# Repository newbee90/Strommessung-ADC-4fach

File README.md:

# Strommessung-ADC-4fach
nach einem Projekt von Jürgen Stähr, L1,L2,L3 und N auf einem Display
Kontaktlose Strommessung mit ADC für 4 Stromwandler
und Anzeige auf einem 2004 Display

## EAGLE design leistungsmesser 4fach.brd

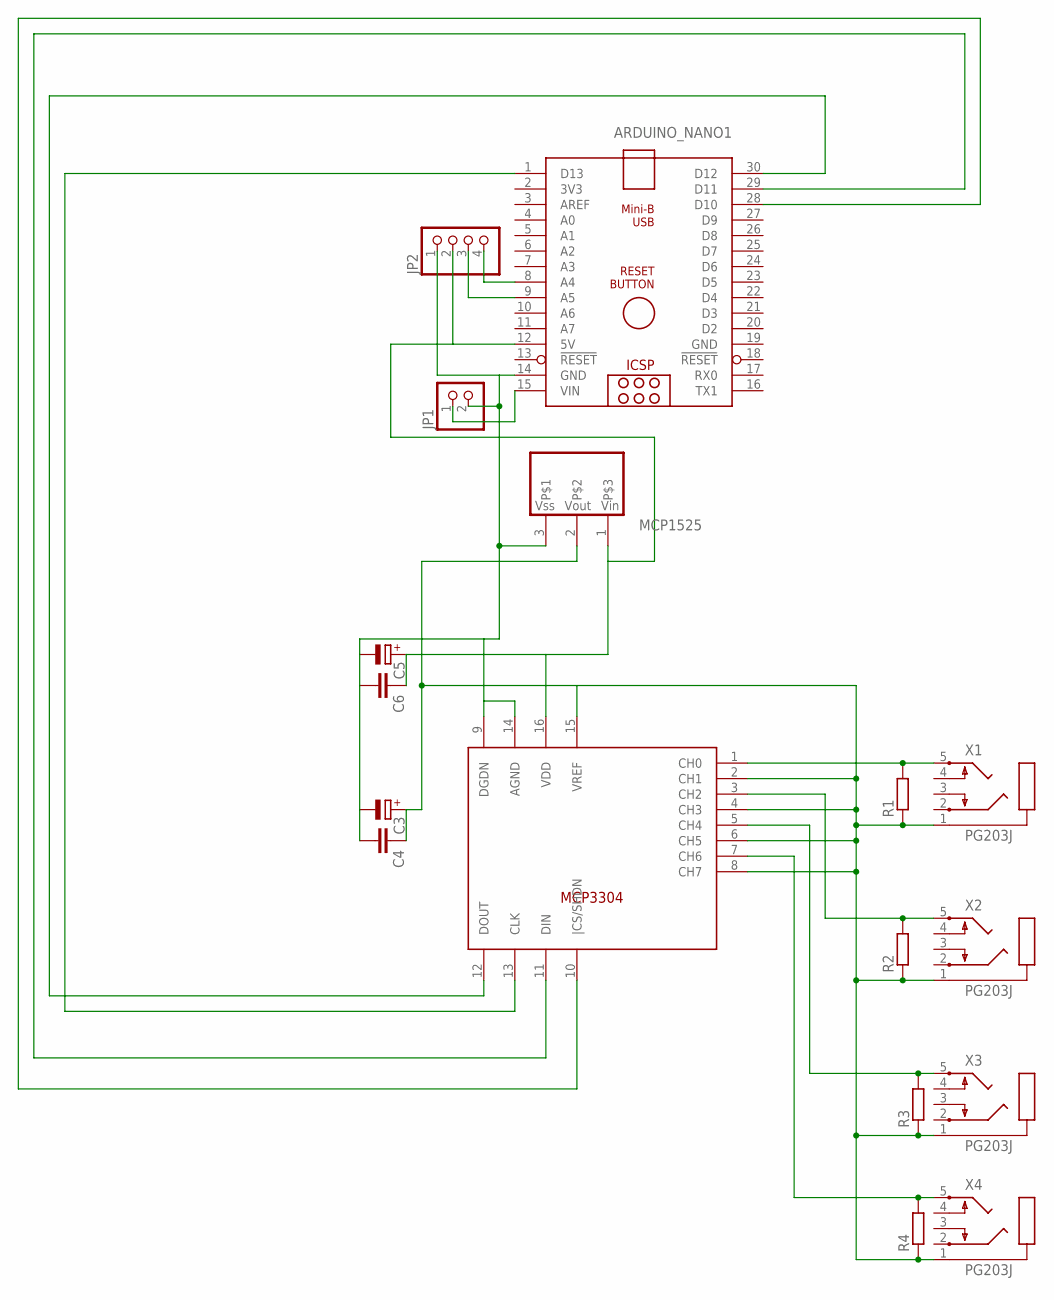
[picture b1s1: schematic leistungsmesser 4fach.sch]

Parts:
ARDUINO_NANO1: ARDUINO_NANO
C3, C5: CPOL-EUE2,5-6E; E2,5-6E
C4, C6: C-EU025-024X044; C025-024X044
IC4: MCP1525; TO92-
JP1: PINHD-1X2; 1X02
JP2: PINHD-1X4; 1X04
R1, R2, R3, R4: R-EU_0309/V; 0309V
U$1: MCP3304; DIP16
X1, X2, X3, X4: PG203J

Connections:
GND: ARDUINO_NANO1.19 (GND)
unnamed: ARDUINO_NANO1.14 (GND), C3.-, C4.2, C5.-, C6.2, IC4.3, JP1.2, JP2.1, U$1.9 (DGDN), U$1.14 (AGND)
unnamed: C3.+, C4.1, IC4.2, R1.1, R2.1, R3.1, R4.1, U$1.2 (CH1), U$1.4 (CH3), U$1.6 (CH5), U$1.8 (CH7), U$1.15 (VREF), X1.1, X2.1, X3.1, X4.1
unnamed: R2.2, U$1.3 (CH2), X2.5
unnamed: ARDUINO_NANO1.30 (D12), U$1.12 (DOUT)
unnamed: ARDUINO_NANO1.15 (VIN), JP1.1
unnamed: ARDUINO_NANO1.28 (D10), U$1.10 (|CS/SHDN)
unnamed: ARDUINO_NANO1.29 (D11), U$1.11 (DIN)
unnamed: ARDUINO_NANO1.1 (D13), U$1.13 (CLK)
unnamed: R3.2, U$1.5 (CH4), X3.5
unnamed: ARDUINO_NANO1.12 (5V), C5.+, C6.1, IC4.1, JP2.2, U$1.16 (VDD)
unnamed: R1.2, U$1.1 (CH0), X1.5
unnamed: R4.2, U$1.7 (CH6), X4.5
unnamed: ARDUINO_NANO1.8 (A4), JP2.4
unnamed: ARDUINO_NANO1.9 (A5), JP2.3

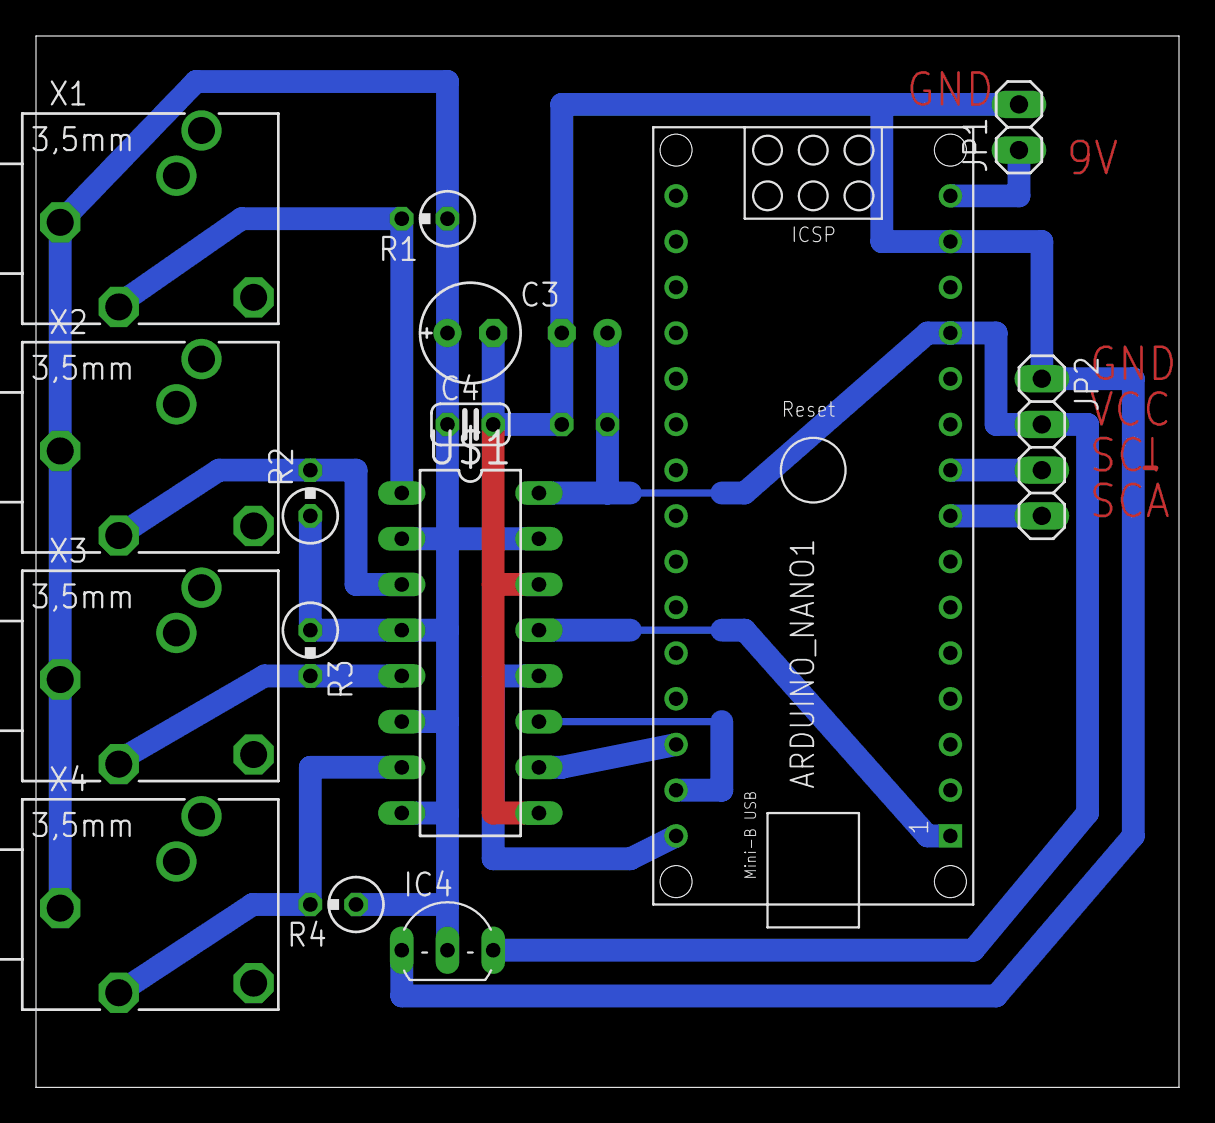
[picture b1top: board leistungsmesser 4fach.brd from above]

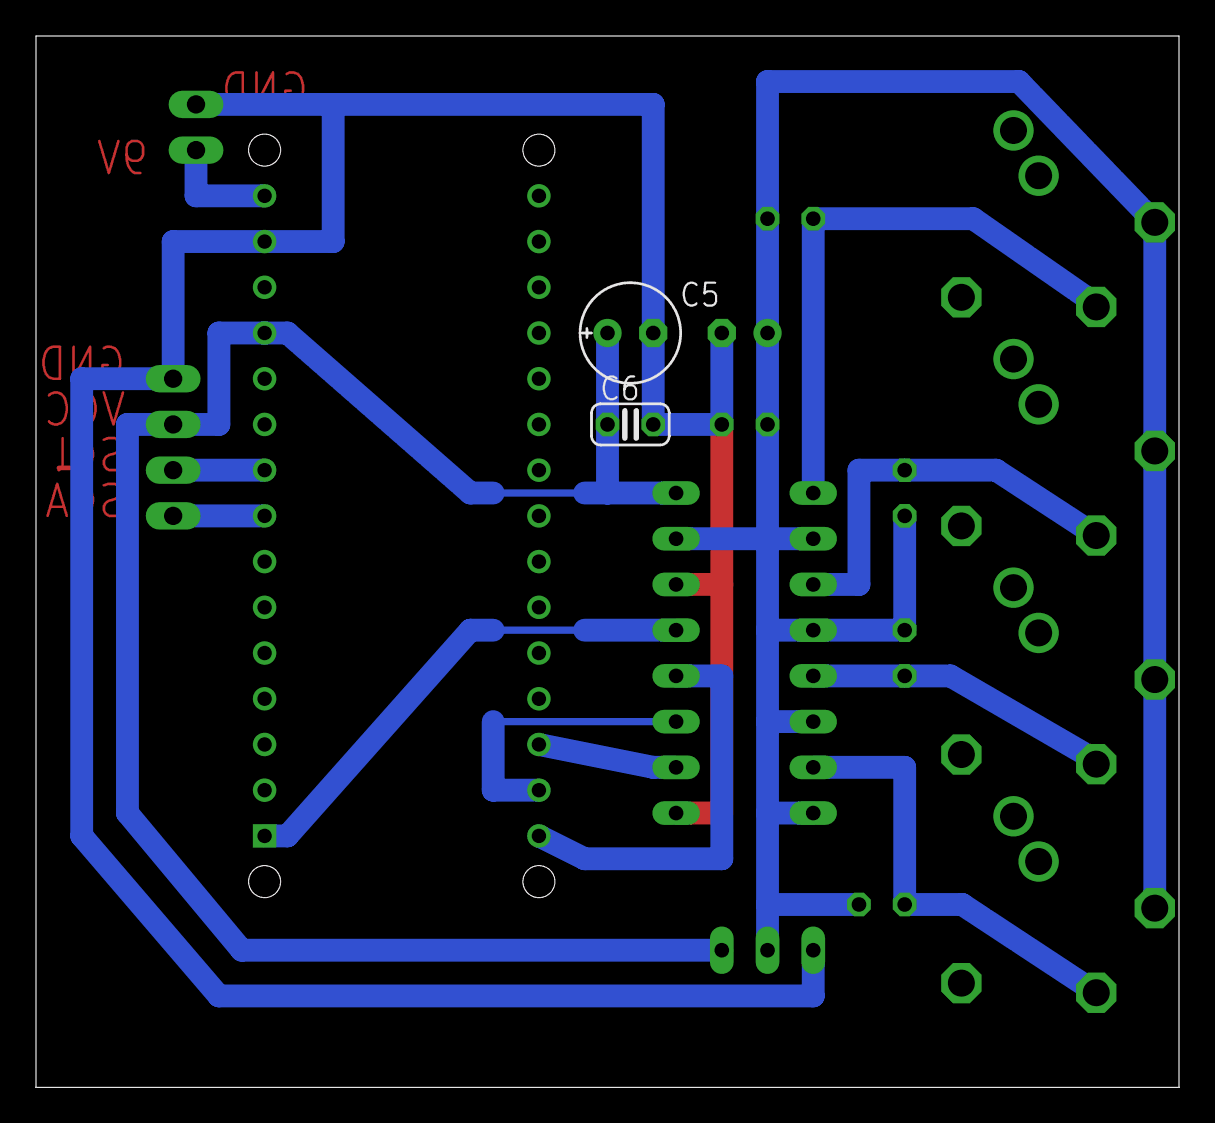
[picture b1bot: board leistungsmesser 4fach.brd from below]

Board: 2 copper layers, 63.5 x 58.4 mm, 17 parts (2 on the bottom side), 14 nets.
